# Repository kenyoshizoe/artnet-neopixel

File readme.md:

# artnet-neopixel
stm32 based Neopixel controller via artnet

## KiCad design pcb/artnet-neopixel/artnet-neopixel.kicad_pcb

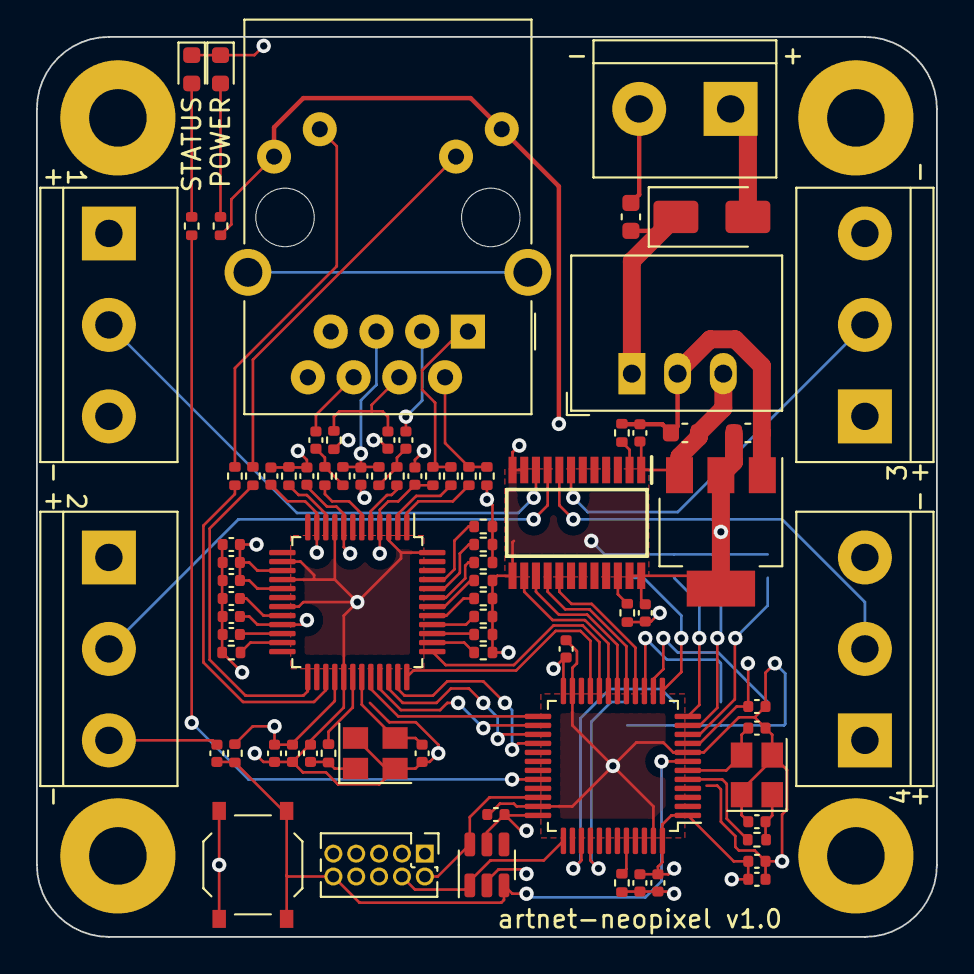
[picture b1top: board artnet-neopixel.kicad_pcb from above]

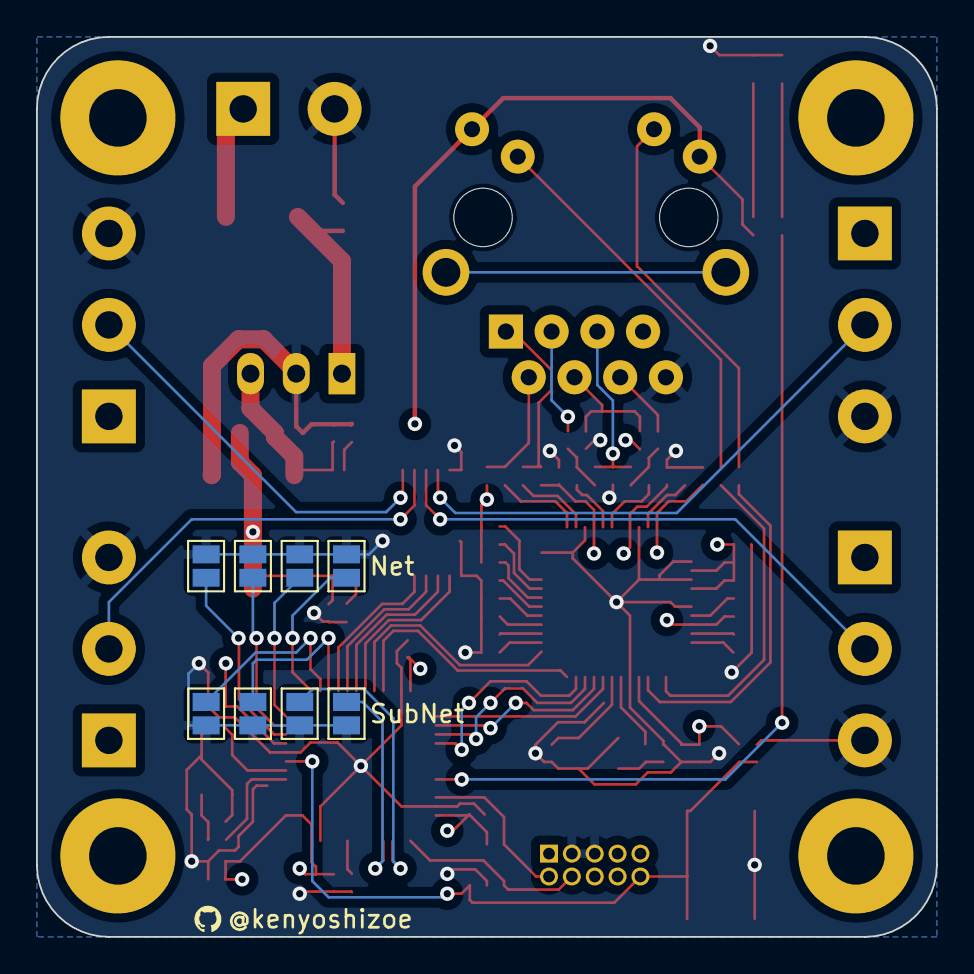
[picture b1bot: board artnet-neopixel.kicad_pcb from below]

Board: 4 copper layers, 50.0 x 50.0 mm, 92 parts (8 on the bottom side), 70 nets.

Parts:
C1: 100n; C_0603_1608Metric
C2, C3: 22uF; C_0603_1608Metric
C4, C32: 4.7u; C_0402_1005Metric
C5, C6, C7, C9, C10, C11, C14, C15, C22, C23, C24, C25, C26, C27, C28, C31: 100n; C_0402_1005Metric
C8: 1u; C_0402_1005Metric
C12, C13, C19, C21: 10p; C_0402_1005Metric
C16, C17: 6.8n; C_0402_1005Metric
C18: 22n; C_0402_1005Metric
C20: 10n; C_0402_1005Metric
C29, C30: 10u; C_0402_1005Metric
D1: SS14; D_SMA
D2: Blue; LED_0603_1608Metric
D3: Green; LED_0603_1608Metric
H1, H2, H3, H4: MountingHole; MountingHole_3.2mm_M3_Pad
IC1: SN74LVC4245APWR; SOP65P640X120-24N
J1: Screw_Terminal_01x02; TerminalBlock_bornier-2_P5.08mm
J2: Conn_02x05_Odd_Even; PinHeader_2x05_P1.27mm_Vertical
J3, J4, J5, J6: Screw_Terminal_01x03; TerminalBlock_bornier-3_P5.08mm
J7: RJ45_Amphenol_RJMG1BD3B8K1ANR
JP1, JP2, JP3, JP4, JP5, JP6, JP7, JP8: Jumper_2_Open; SolderJumper-2_P1.3mm_Open_Pad1.0x1.5mm
R1, R2, R4, R5, R6, R7, R19, R20, R22: 1k; R_0402_1005Metric
R3, R17, R18, R21, R23, R24, R25, R26, R27, R28: 10k; R_0402_1005Metric
R8, R9, R15, R16: 49.9; R_0402_1005Metric
R10: 10; R_0402_1005Metric
R11, R12, R13, R14: 33; R_0402_1005Metric
R29: 12k; R_0402_1005Metric
SW1: RESET; SW_Push_1P1T_XKB_TS-1187A
U1: R-783.3-0.5; Converter_DCDC_RECOM_R-78E-0.5_THT
U2: AMS1117-3.3; SOT-223-3_TabPin2
U3: SRV05-4; SOT-23-6
U4: STM32F303CBTx; LQFP-48_7x7mm_P0.5mm
U5: W5500; LQFP-48_7x7mm_P0.5mm
Y1: 16MHz; Crystal_SMD_3225-4Pin_3.2x2.5mm
Y2: 25MHz; Crystal_SMD_3225-4Pin_3.2x2.5mm

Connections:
+3.3V: C3.1, C4.1, C5.1, C6.1, C7.1, C8.1, C9.1, C10.1, C15.1, C22.1, C23.1, C24.1, C25.1, C26.1, C27.1, C28.1, C29.1, C30.1, IC1.23 (VCCB_1), IC1.24 (VCCB_2), J2.1, J7.L1 (LEDY_A), J7.L4 (LEDG_A), R1.1, R3.2, R8.1, R9.1, R10.1, R17.1, R18.1, R21.1, U2.2 (VO), U3.5 (VP), U4.1 (VBAT), U4.9 (VDDA), U4.24 (VDD), U4.36 (VDD), U4.48 (VDD), U5.4 (AVDD), U5.8 (AVDD), U5.11 (AVDD), U5.15 (AVDD), U5.17 (AVDD), U5.21 (AVDD), U5.28 (VDD)
+5V: C2.1, C14.1, IC1.1 (VCCA), U1.3 (OUT), U2.3 (VI)
+24V: D1.2 (A), J1.1, J3.1, J4.1, J5.1, J6.1
ACT_LED: R22.2, U5.27 (ACTLED)
BOOT: R6.1, U4.44 (BOOT0)
CS: U4.25 (PB12), U5.32 (~SCS)
GND: C1.2, C2.2, C3.2, C4.2, C5.2, C6.2, C7.2, C8.2, C9.2, C10.2, C11.2, C12.2, C13.2, C14.2, C15.2, C18.2, C19.2, C20.2, C21.2, C22.2, C23.2, C24.2, C25.2, C26.2, C27.2, C28.2, C29.2, C30.2, C31.1, C32.2, D2.1 (K), D3.1 (K), IC1.11 (GND_1), IC1.12 (GND_2), IC1.13 (GND_3), J1.2, J2.3, J2.5, J3.3, J4.3, J5.3, J6.3, J7.R8 (GND), JP1.2 (B), JP2.2 (B), JP3.2 (B), JP4.2 (B), JP5.2 (B), JP6.2 (B), JP7.2 (B), JP8.2 (B), R4.1, R6.2, R7.2, R23.1, R24.1, R25.1, R26.1, R27.1, R28.1, R29.1, SW1.2, U1.2 (GND), U2.1 (GND), U3.2 (VN), U4.8 (VSSA), U4.23 (VSS), U4.35 (VSS), U4.47 (VSS), U5.3 (AGND), U5.9 (AGND), U5.14 (AGND), U5.16 (AGND), U5.19 (AGND), U5.29 (GND), U5.48 (AGND), Y1.2, Y1.4, Y2.2, Y2.4
JP1: JP1.1 (A), U4.10 (PA0)
JP2: JP2.1 (A), U4.11 (PA1)
JP3: JP3.1 (A), U4.12 (PA2)
JP4: JP4.1 (A), U4.13 (PA3)
JP5: JP5.1 (A), U4.14 (PA4)
JP6: JP6.1 (A), U4.15 (PA5)
JP7: JP7.1 (A), U4.39 (PB3)
JP8: JP8.1 (A), U4.40 (PB4)
LINK_LED: R19.2, U5.25 (LINKLED)
MISO: U4.27 (PB14), U5.34 (MISO)
MOSI: U4.28 (PB15), U5.35 (MOSI)
NRST: C11.1, J2.10, R3.1, SW1.1, U3.3 (IO2), U4.7 (NRST)
unnamed: C12.1, R5.1, Y1.1
unnamed: C16.2, R13.2, R15.1
unnamed: C17.2, R14.2, R16.1
unnamed: C19.1, R20.1, Y2.1
unnamed: C1.1, D1.1 (K), U1.1 (IN)
unnamed: D2.2 (A), R1.2
unnamed: D3.2 (A), R2.2
unnamed: IC1.7 (A5), J3.2
unnamed: IC1.8 (A6), J4.2
unnamed: IC1.9 (A7), J5.2
unnamed: IC1.10 (A8), J6.2
unnamed: IC1.2 (DIR), R4.2
unnamed: IC1.22 (~OE), R7.1
unnamed: J7.L3 (LEDG_K), R19.1
unnamed: J7.L2 (LEDY_K), R22.1
unnamed: C20.1, J7.R5 (RCT), R15.2, R16.2
unnamed: C16.1, J7.R3 (RD+)
unnamed: C17.1, J7.R6 (RD-)
unnamed: C18.1, J7.R4 (TCT), R10.2
unnamed: J7.R1 (TD+), R9.2, R12.2
unnamed: J7.R2 (TD-), R8.2, R11.2
unnamed: R23.2, U5.38 (RSVD)
unnamed: R24.2, U5.39 (RSVD)
unnamed: R25.2, U5.40 (RSVD)
unnamed: R26.2, U5.41 (RSVD)
unnamed: R27.2, U5.42 (RSVD)
unnamed: R28.2, U5.23 (RSVD)
unnamed: C31.2, U5.22 (1V2O)
unnamed: R29.2, U5.10 (EXRES1)
unnamed: R17.2, U5.45 (PMODE0)
unnamed: R18.2, U5.44 (PMODE1)
unnamed: R21.2, U5.43 (PMODE2)
unnamed: R13.1, U5.5 (RXN)
unnamed: R14.1, U5.6 (RXP)
unnamed: C32.1, U5.20 (TOCAP)
unnamed: R11.1, U5.1 (TXN)
unnamed: R12.1, U5.2 (TXP)
unnamed: R20.2, U5.30 (XI/CLKIN)
unnamed: C21.1, U5.31 (XO), Y2.3
OSC_IN: R5.2, U4.5 (PF0)
OSC_OUT: C13.1, U4.6 (PF1), Y1.3
RUN_LED: R2.1, U4.32 (PA11)
SCLK: U4.26 (PB13), U5.33 (SCLK)
SWCLK: J2.4, U3.1 (IO1), U4.37 (PA14)
SWDIO: J2.2, U3.6 (IO4), U4.34 (PA13)
W5500_INT: U4.21 (PB10), U5.36 (~INT)
W5500_RST: U4.20 (PB2), U5.37 (~RST)
neopixel1: IC1.15 (B7), U4.18 (PB0)
neopixel2: IC1.14 (B8), U4.19 (PB1)
neopixel3: IC1.16 (B6), U4.17 (PA7)
neopixel4: IC1.17 (B5), U4.16 (PA6)

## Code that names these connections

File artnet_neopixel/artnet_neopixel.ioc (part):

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Mcu.Name=STM32F303C(B-C)Tx
Mcu.Package=LQFP48
Mcu.UserName=STM32F303CBTx
PA0.GPIOParameters=GPIO_PuPd,GPIO_Label
PA0.GPIO_Label=NET0
PA0.GPIO_PuPd=GPIO_PULLUP
PA0.Signal=GPIO_Input
PA1.GPIOParameters=GPIO_PuPd,GPIO_Label
PA1.GPIO_Label=NET1
PA1.GPIO_PuPd=GPIO_PULLUP
PA1.Signal=GPIO_Input
PA11.GPIOParameters=GPIO_Label
PA11.GPIO_Label=RUN_LED
PA11.Signal=GPIO_Output
PA13.Mode=Serial_Wire
PA13.Signal=SYS_JTMS-SWDIO
PA14.Mode=Serial_Wire
PA14.Signal=SYS_JTCK-SWCLK
PA2.GPIOParameters=GPIO_PuPd,GPIO_Label
PA2.GPIO_Label=NET2
PA2.GPIO_PuPd=GPIO_PULLUP
PA2.Signal=GPIO_Input
PA3.GPIOParameters=GPIO_PuPd,GPIO_Label
PA3.GPIO_Label=NET3
PA3.GPIO_PuPd=GPIO_PULLUP
PA3.Signal=GPIO_Input
PA4.GPIOParameters=GPIO_PuPd,GPIO_Label
PA4.GPIO_Label=SUBNET0
PA4.GPIO_PuPd=GPIO_PULLUP
PA4.Signal=GPIO_Input
PA5.GPIOParameters=GPIO_PuPd,GPIO_Label
PA5.GPIO_Label=SUBNET1
PA5.GPIO_PuPd=GPIO_PULLUP
PA5.Signal=GPIO_Input
PA6.GPIOParameters=GPIO_Speed,GPIO_Label
PA6.GPIO_Label=NEOPIXEL3
PA6.GPIO_Speed=GPIO_SPEED_FREQ_HIGH
PA6.Signal=S_TIM3_CH1
PA7.GPIOParameters=GPIO_Speed,GPIO_Label
PA7.GPIO_Label=NEOPIXEL4
PA7.GPIO_Speed=GPIO_SPEED_FREQ_HIGH
PA7.Signal=S_TIM17_CH1
PB0.GPIOParameters=GPIO_Speed,GPIO_PuPd,GPIO_Label
PB0.GPIO_Label=NEOPIXEL2
PB0.GPIO_PuPd=GPIO_NOPULL
PB0.GPIO_Speed=GPIO_SPEED_FREQ_HIGH
PB0.Signal=S_TIM3_CH3
PB1.GPIOParameters=GPIO_Speed,GPIO_Label
PB1.GPIO_Label=NEOPIXEL1
PB1.GPIO_Speed=GPIO_SPEED_FREQ_HIGH
PB1.Signal=S_TIM3_CH4
PB10.GPIOParameters=GPIO_Label
PB10.GPIO_Label=W5500_ITR
PB10.Signal=GPIO_Input
PB12.GPIOParameters=GPIO_Label
PB12.GPIO_Label=W5500_CS
PB12.Signal=GPIO_Output
PB13.Mode=Full_Duplex_Master
PB13.Signal=SPI2_SCK
PB14.Mode=Full_Duplex_Master
PB14.Signal=SPI2_MISO
PB15.Mode=Full_Duplex_Master
PB15.Signal=SPI2_MOSI
PB2.GPIOParameters=GPIO_Label
PB2.GPIO_Label=W5500_RESET
PB2.Signal=GPIO_Output
PB3.GPIOParameters=GPIO_PuPd,GPIO_Label
PB3.GPIO_Label=SUBNET2
PB3.GPIO_PuPd=GPIO_PULLUP
PB3.Signal=GPIO_Input
PB4.GPIOParameters=GPIO_PuPd,GPIO_Label
PB4.GPIO_Label=SUBNET3
PB4.GPIO_PuPd=GPIO_PULLUP
PB4.Signal=GPIO_Input
PF0-OSC_IN.Mode=HSE-External-Oscillator
PF0-OSC_IN.Signal=RCC_OSC_IN
PF1-OSC_OUT.Mode=HSE-External-Oscillator
PF1-OSC_OUT.Signal=RCC_OSC_OUT
RCC.HSEPLLFreq_Value=16000000
RCC.HSE_VALUE=16000000
RCC.SYSCLKFreq_VALUE=32000000
RCC.SYSCLKSourceVirtual=RCC_SYSCLKSOURCE_PLLCLK
board=custom

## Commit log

2024-06-29 :tada: add artnet-neopixel pcb design
2024-06-29 :sparkles: pcb v1.0
2024-06-29 :memo: add readme
2024-07-01 :tada: configure cube mx & setup makefile
2024-07-01 :heavy_plus_sign: add segger_rtt
2024-07-01 :wrench: configure ldflags
2024-07-05 :wrench: add --print-memory-usage to ld flag
2024-07-06 :heavy_plus_sign: add etl as submodule
2024-07-06 :tada: add neopixel
2024-07-06 :bug: fix neopixel
2024-07-07 :tada: add w5500
2024-07-07 :heavy_plus_sign: add ArtNode
2024-07-07 :tada: add artnet-neopixel
2024-07-08 :recycle: refactor
2024-07-08 :sparkles: add net / subnet jumper read
